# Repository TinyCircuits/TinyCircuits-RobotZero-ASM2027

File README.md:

# TinyCircuits RobotZero ASM2027
# ASM2026 Rev3

The design files are located under design_files/ for the TinyCircuits ASM2027 Rev 4 PCB, and Rev3 schematic pdf. This is a processor board with several different connectors (for Motors, Servos, and [Wirelings](https://tinycircuits.com/pages/wireling-overview)) that add a great range of customizable functionality.

Format is in Cadsoft Eagle format - Eagle version 6.2 was used for the original design.

For more infomation on this, check out the product page at TinyCircuits.com

# License:

Design by TinyCircuits.
All design files are released under the Creative Commons Attribution Share-Alike 3.0 License, see the following link for details: http://creativecommons.org/licenses/by-sa/3.0

All text above must be included in any redistribution or derived design

This project uses designs and concepts developed as part of the Arduino project and the LilyPad project.  The TinyCircuits design files themselves (schematics, PCB and libraries) are not directly derived from these works' design files and have been created new, however the concepts and basic architecture behind the TinyDuino and TinyLily products are derived and we thank the hard work of the organizations below for their contributions to open-source hardware:
  
Original Arduino Uno Design by Team Arduino

LilyPad Arduino Design by Leah Buechley and Sparkfun Electronics

Please support the open-source hardware community

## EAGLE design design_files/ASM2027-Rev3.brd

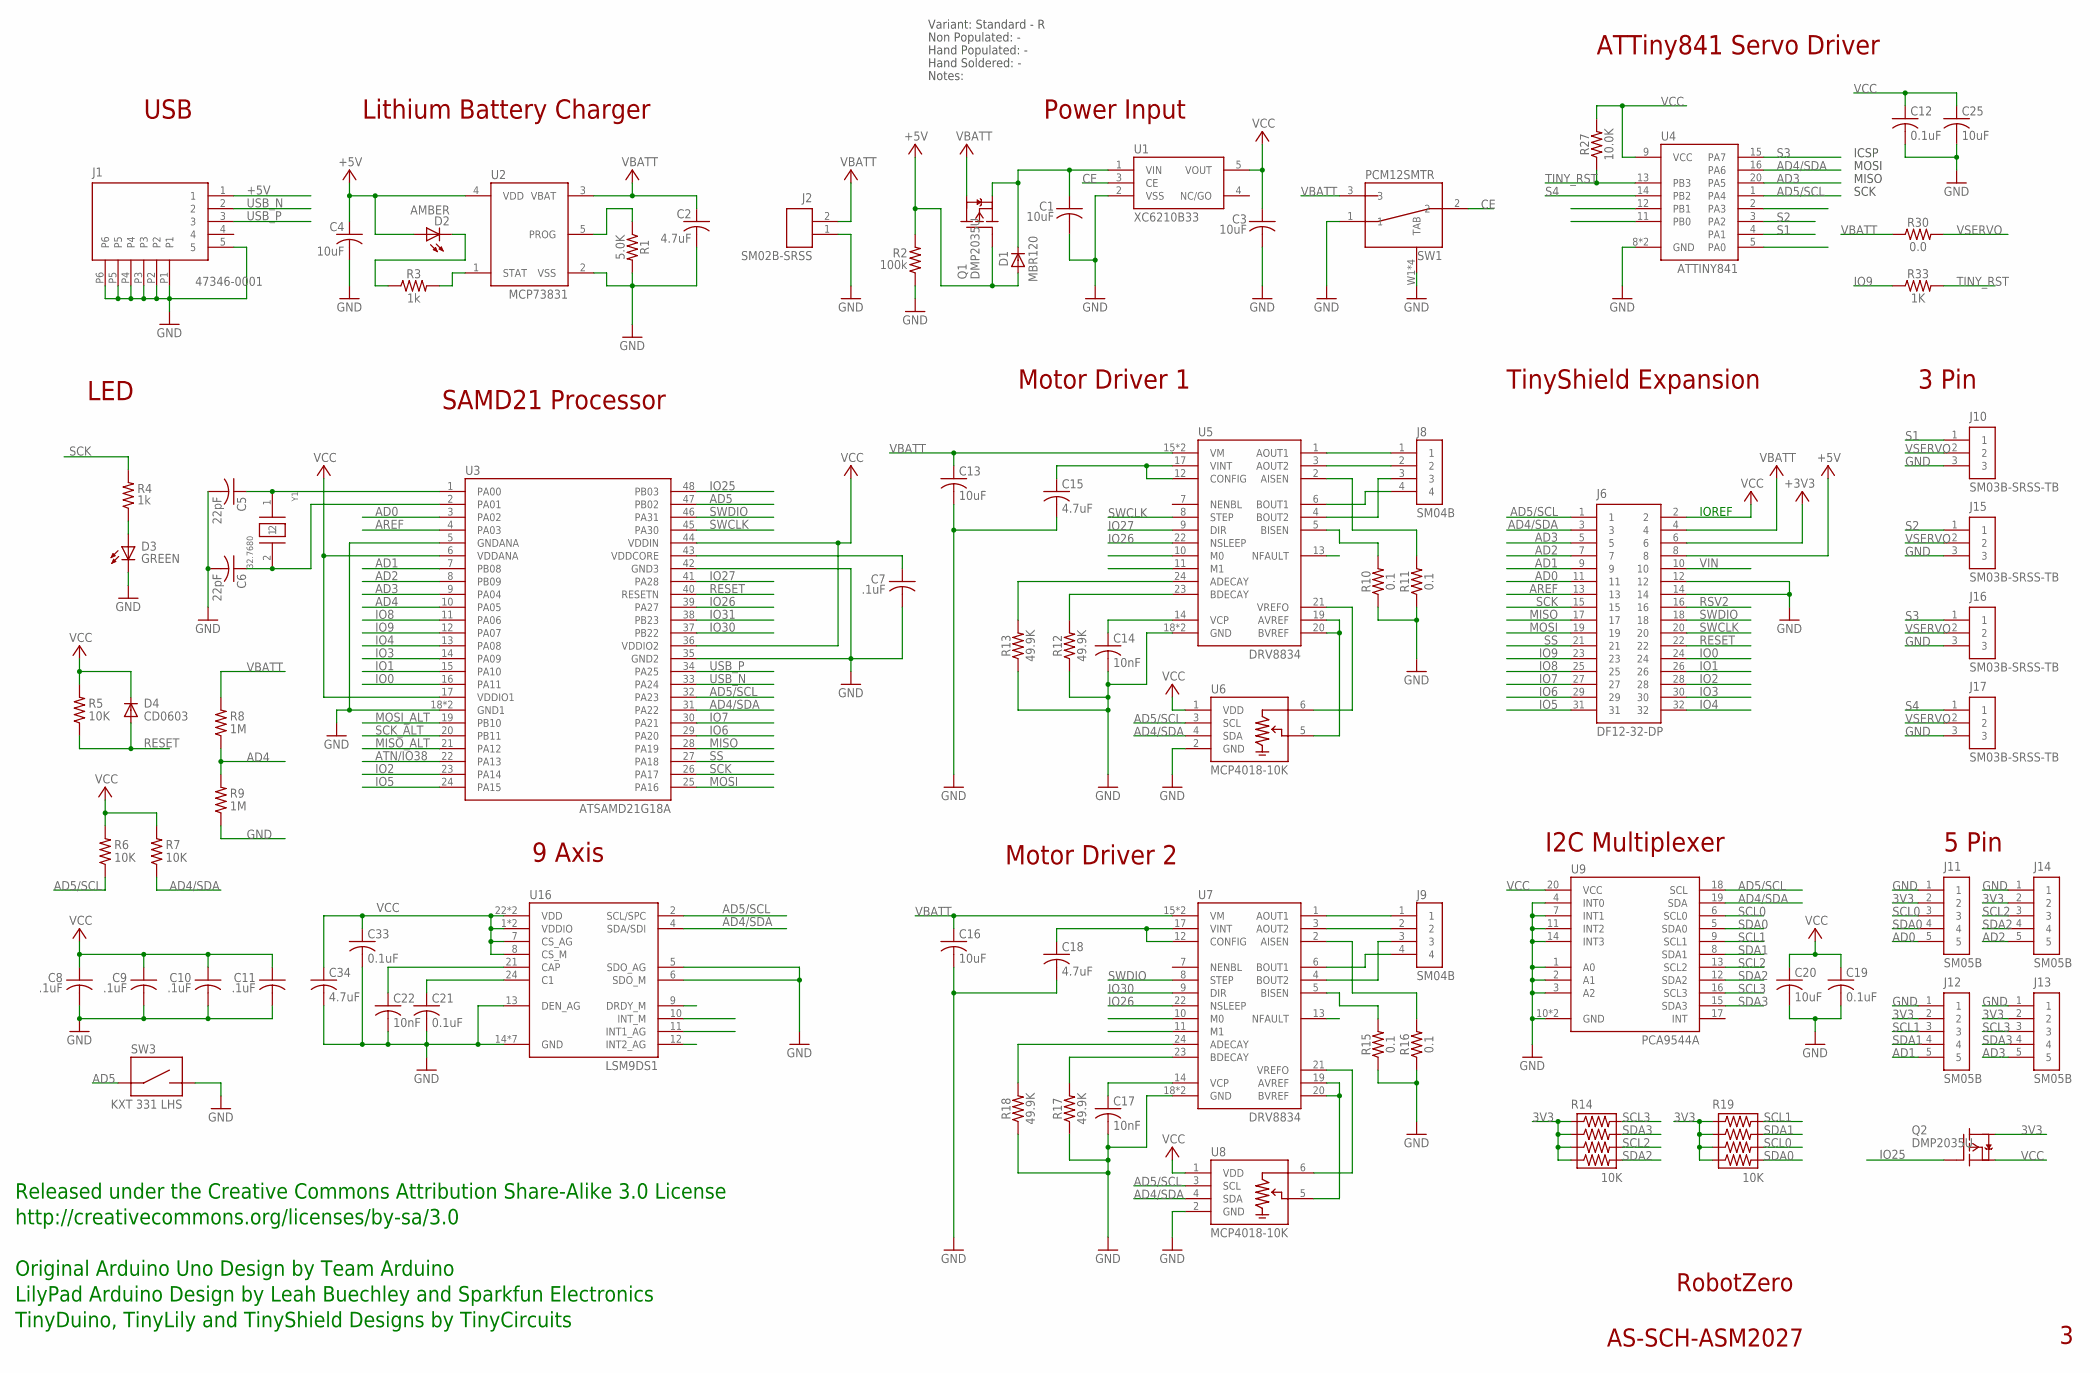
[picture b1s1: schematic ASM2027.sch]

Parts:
C1, C3, C4: 10uF; C0603; PARTNO AS-ITM-00002
C2: 4.7uF; C0603; PARTNO AS-ITM-00088
C5, C6: 22pF; C0402; PARTNO AS-ITM-00211
C7, C8, C9, C10, C11: .1uF; C0402; PARTNO AS-ITM-00008
C12, C19, C21: 0.1uF; C0402
C13, C16, C20: 10uF; C0603
C14, C17, C22: 10nF; C0402
C15, C18: 4.7uF; C0402
C25: 10uF; C0805
C33: 0.1uF; C0402; PARTNO AS-ITM-00008
C34: 4.7uF; C0402; PARTNO AS-ITM-00242
D1: MBR120; SOD-123FL
D2: AMBER; 0402_LED; PARTNO AS-ITM-00058
D3: GREEN; LNJ_LED; PARTNO AS-ITM-00011
D4: CD0603; 0603; PARTNO AS-ITM-00009
J1: 47346-0001; MICRO_USB
J2: SM02B-SRSS; JST_SH_2X1
J6: DF12-32-DP; PARTNO AS-ITM-00015
J8, J9: SM04B; JST_SH_4X1; PARTNO AS-ITM-00395
J10, J15, J16, J17: SM03B-SRSS-TB; JST_SH_3X1_VERT; PARTNO AS-ITM-00471
J11, J12, J13, J14: SM05B; JST_SH_5X1_VERT; PARTNO AS-ITM-00391
Q1, Q2: DMP2035U; SOT23A; PARTNO AS-ITM-00024
R1: 5.0K; 0402; PARTNO AS-ITM-00289
R2: 100k; 0402; PARTNO AS-ITM-00004
R3, R4: 1k; 0402; PARTNO AS-ITM-00003
R5, R6, R7: 10K; 0402; PARTNO AS-ITM-00032
R8, R9: 1M; 0402; PARTNO AS-ITM-00005
R10, R11, R15, R16: 0.1; R0805
R12, R13, R17, R18: 49.9K; 0402
R14, R19: 10K; 0402RPACK; PARTNO AS-ITM-00520
R27: 10.0K; 0402
R30: 0.0; 0402
R33: 1K; 0402
SW1: PCM12SMTR
SW3: KXT 331 LHS; KXT_LHS
U1: XC6210B33; SOT-25
U2: MCP73831; SOT-23
U3: ATSAMD21G18A; QFN48; PARTNO AS-ITM-00273
U4: ATTINY841; VQFN-20
U5, U7: DRV8834; VQFN-24_4X4
U6, U8: MCP4018-10K; SOT-353-6
U9: PCA9544A; VQFN-20_4.5X3.5
U16: LSM9DS1; LGA-24
Y1: 32.7680; ABS06; PARTNO AS-ITM-00279

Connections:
3V3: J11.2, J12.2, J13.2, J14.2, Q2.C (D), R14.1, R14.3, R14.5, R14.7, R19.1, R19.3, R19.5, R19.7
+3V3: J6.6
+5V: C4.1, D1.A, D2.1 (A), J1.1, J6.8, Q1.B (G), R2.2, U2.4 (VDD)
AD0: J6.11, J11.5, U3.3 (PA02)
AD1: J6.9, J12.5, U3.7 (PB08)
AD2: J6.7, J14.5, U3.8 (PB09)
AD3: J6.5, J13.5, U3.9 (PA04), U4.20 (PA5)
AD4: R8.1, R9.2, U3.10 (PA05)
AD4/SDA: J6.3, R7.1, U3.31 (PA22), U4.16 (PA6), U6.4 (SDA), U8.4 (SDA), U9.19 (SDA), U16.4 (SDA/SDI)
AD5: SW3.1, U3.47 (PB02)
AD5/SCL: J6.1, R6.1, U3.32 (PA23), U4.1 (PA4), U6.3 (SCL), U8.3 (SCL), U9.18 (SCL), U16.2 (SCL/SPC)
AOUT1: J8.1, U5.1 (AOUT1)
AOUT2: J8.2, U5.3 (AOUT2)
AOUT3: J9.1, U7.1 (AOUT1)
AREF: J6.13, U3.4 (PA03)
ATN/IO38: U3.22 (PA13)
BOUT1: J8.4, U5.6 (BOUT1)
BOUT2: J8.3, U5.4 (BOUT2)
BOUT3: J9.4, U7.6 (BOUT1)
BOUT4: J9.3, U7.4 (BOUT2)
CE: SW1.2, U1.3 (CE)
GND: C1.2, C2.2, C3.2, C4.2, C5.2, C6.2, C7.2, C8.2, C9.2, C10.2, C11.2, C12.2, C13.2, C14.2, C15.2, C16.2, C17.2, C18.2, C19.2, C20.2, C21.2, C22.2, C25.2, C33.2, C34.2, D3.C, J1.5, J1.P1, J1.P2, J1.P3, J1.P4, J1.P5, J1.P6, J2.1 (2), J6.12, J6.14, J10.3, J11.1, J12.1, J13.1, J14.1, J15.3, J16.3, J17.3, R1.2, R2.1, R9.1, R10.1, R11.1, R12.1, R13.1, R15.1, R16.1, R17.1, R18.1, SW1.1, SW1.W1 (TAB), SW1.W2 (TAB), SW1.W3 (TAB), SW1.W4 (TAB), SW3.2, U1.2 (VSS), U2.2 (VSS), U3.5 (GNDANA), U3.18 (GND1), U3.35 (GND2), U3.42 (GND3), U3.EXP (GND1), U4.8 (GND), U4.PAD (GND), U5.18 (GND), U5.PAD (GND), U6.2 (GND), U7.18 (GND), U7.PAD (GND), U8.2 (GND), U9.1 (A0), U9.2 (A1), U9.3 (A2), U9.4 (INT0), U9.7 (INT1), U9.10 (GND), U9.11 (INT2), U9.14 (INT3), U9.PAD (GND), U16.5 (SDO_AG), U16.6 (SDO_M), U16.13 (DEN_AG), U16.14 (GND), U16.15 (GND), U16.16 (GND), U16.17 (GND), U16.18 (GND), U16.19 (GND), U16.20 (GND)
IO0: J6.24, U3.16 (PA11)
IO1: J6.26, U3.15 (PA10)
IO2: J6.28, U3.23 (PA14)
IO3: J6.30, U3.14 (PA09)
IO4: J6.32, U3.13 (PA08)
IO5: J6.31, U3.24 (PA15)
IO6: J6.29, U3.29 (PA20)
IO7: J6.27, U3.30 (PA21)
IO8: J6.25, U3.11 (PA06)
IO9: J6.23, R33.1, U3.12 (PA07)
IO25: Q2.B (G), U3.48 (PB03)
IO26: U3.39 (PA27), U5.22 (NSLEEP), U7.22 (NSLEEP)
IO27: U3.41 (PA28), U5.9 (DIR)
IO30: U3.37 (PB22), U7.9 (DIR)
IO31: U3.38 (PB23)
MISO: J6.17, U3.28 (PA19)
MISO_ALT: U3.21 (PA12)
MOSI: J6.19, U3.25 (PA16)
MOSI_ALT: U3.19 (PB10)
unnamed: C5.1, U3.1 (PA00), Y1.1
unnamed: C6.1, U3.2 (PA01), Y1.2
unnamed: D3.A, R4.1
unnamed: D2.2 (C), R3.1
unnamed: R1.1, U2.5 (PROG)
unnamed: R3.2, U2.1 (STAT)
unnamed: C7.1, U3.43 (VDDCORE)
unnamed: R10.2, U5.5 (BISEN)
unnamed: R11.2, U5.2 (AISEN)
unnamed: U5.19 (AVREF), U5.20 (BVREF), U6.5 (W)
unnamed: U5.21 (VREFO), U6.6 (A)
unnamed: C14.1, U5.14 (VCP)
unnamed: R12.2, U5.23 (BDECAY)
unnamed: R13.2, U5.24 (ADECAY)
unnamed: J9.2, U7.3 (AOUT2)
unnamed: C15.1, U5.12 (CONFIG), U5.17 (VINT)
unnamed: R15.2, U7.5 (BISEN)
unnamed: R16.2, U7.2 (AISEN)
unnamed: U7.19 (AVREF), U7.20 (BVREF), U8.5 (W)
unnamed: U7.21 (VREFO), U8.6 (A)
unnamed: C17.1, U7.14 (VCP)
unnamed: R17.2, U7.23 (BDECAY)
unnamed: R18.2, U7.24 (ADECAY)
unnamed: C18.1, U7.12 (CONFIG), U7.17 (VINT)
unnamed: C22.1, U16.21 (CAP)
unnamed: C21.1, U16.24 (C1)
RESET: D4.A, J6.22, R5.1, U3.40 (RESETN)
RSV2: J6.16
S1: J10.1, U4.4 (PA1)
S2: J15.1, U4.3 (PA2)
S3: J16.1, U4.15 (PA7)
S4: J17.1, U4.14 (PB2)
SCK: J6.15, R4.2, U3.26 (PA17)
SCK_ALT: U3.20 (PB11)
SCL0: J11.3, R19.6, U9.6 (SCL0)
SCL1: J12.3, R19.2, U9.9 (SCL1)
SCL2: J14.3, R14.6, U9.13 (SCL2)
SCL3: J13.3, R14.2, U9.16 (SCL3)
SDA0: J11.4, R19.8, U9.5 (SDA0)
SDA1: J12.4, R19.4, U9.8 (SDA1)
SDA2: J14.4, R14.8, U9.12 (SDA2)
SDA3: J13.4, R14.4, U9.15 (SDA3)
SS: J6.21, U3.27 (PA18)
SWCLK: J6.20, U3.45 (PA30), U5.8 (STEP)
SWDIO: J6.18, U3.46 (PA31), U7.8 (STEP)
TINY_RST: R27.1, R33.2, U4.13 (PB3)
USB_N: J1.2, U3.33 (PA24)
USB_P: J1.3, U3.34 (PA25)
VBATT: C2.1, C13.1, C16.1, J2.2 (1), J6.4, Q1.C (D), R8.2, R30.1, SW1.3, U2.3 (VBAT), U5.15 (VM), U5.16 (VM), U7.15 (VM), U7.16 (VM)
VCC: C3.1, C8.1, C9.1, C10.1, C11.1, C12.1, C19.1, C20.1, C25.1, C33.1, C34.1, D4.C, J6.2, Q2.E (S), R5.2, R6.2, R7.2, R27.2, U1.5 (VOUT), U3.6 (VDDANA), U3.17 (VDDIO1), U3.36 (VDDIO2), U3.44 (VDDIN), U4.9 (VCC), U6.1 (VDD), U8.1 (VDD), U9.20 (VCC), U16.1 (VDDIO), U16.3 (VDDIO), U16.7 (CS_AG), U16.8 (CS_M), U16.22 (VDD), U16.23 (VDD)
VCC_IN: C1.1, D1.C, Q1.E (S), U1.1 (VIN)
VIN: J6.10
VSERVO: J10.2, J15.2, J16.2, J17.2, R30.2

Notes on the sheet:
IOREF
TinyShield Expansion
SAMD21 Processor
Power Input
LED
RobotZero
AS-SCH-ASM2027
Released under the Creative Commons Attribution Share-Alike 3.0 License
http://creativecommons.org/licenses/by-sa/3.0
Original Arduino Uno Design by Team Arduino
TinyDuino, TinyLily and TinyShield Designs by TinyCircuits
LilyPad Arduino Design by Leah Buechley and Sparkfun Electronics
Lithium Battery Charger
USB
9 Axis
I2C Multiplexer
5 Pin
Motor Driver 1
Motor Driver 2
Non Populated: -
Hand Populated: -
Hand Soldered: -
Notes:
Variant: Standard - R
ATTiny841 Servo Driver
MOSI
MISO
SCK
ICSP
3 Pin

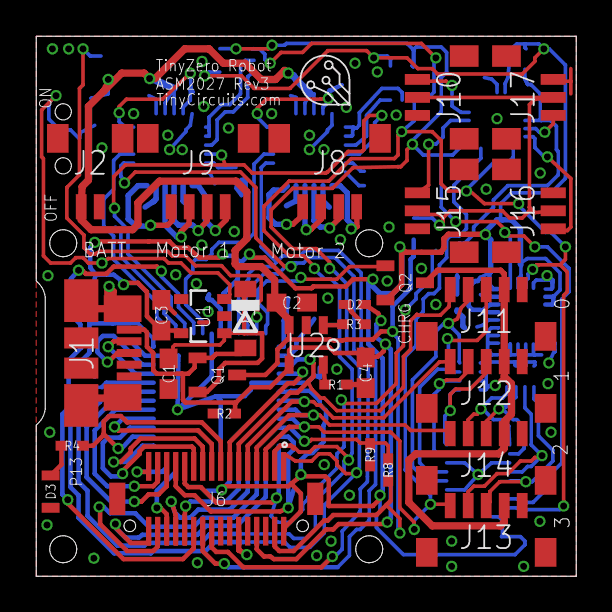
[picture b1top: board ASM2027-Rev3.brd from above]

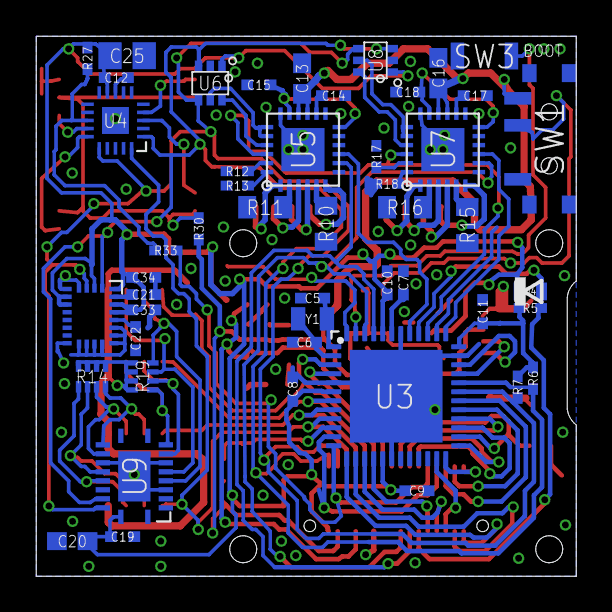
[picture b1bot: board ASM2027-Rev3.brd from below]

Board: 2 copper layers, 30.0 x 30.0 mm, 80 parts (49 on the bottom side), 86 nets.

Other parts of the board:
U$1: DOCFIELD-TINYCIRCUITS-PCB

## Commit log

2019-08-19 initialize
2020-01-15 design & pics
2020-01-15 images
2020-01-15 better pic pls
2020-01-17 program
2020-01-17 naming
2020-03-02 servo example
2020-03-02 servo
2020-06-26 Add CAD data
2020-06-29 Rename files and use different 2D drawing template
2020-06-30 Add compact dimensions in dark & light, and remove vias from models/drawings
2020-06-30 Use png compression to reduce file size of compact dimension images
2020-06-30 Add text to tell what scale preview views are in
2020-07-01 Update preview, remove file
2020-07-02 Add zip of all CAD files
2020-08-18 Update CAD drawings
2020-09-30 add DC motor instructions
2020-11-19 dc motor updates
2022-01-18 fix motor datasheets and update hardware files
